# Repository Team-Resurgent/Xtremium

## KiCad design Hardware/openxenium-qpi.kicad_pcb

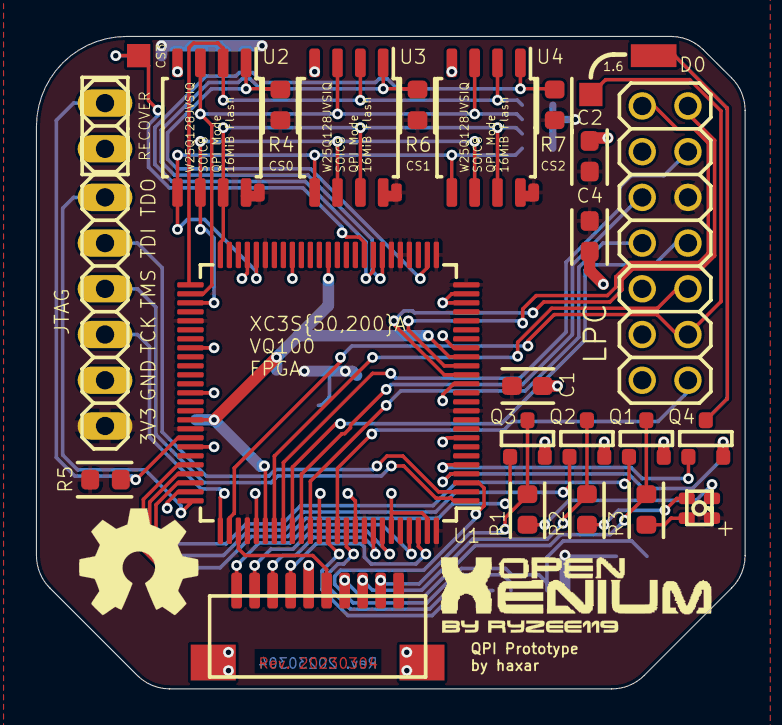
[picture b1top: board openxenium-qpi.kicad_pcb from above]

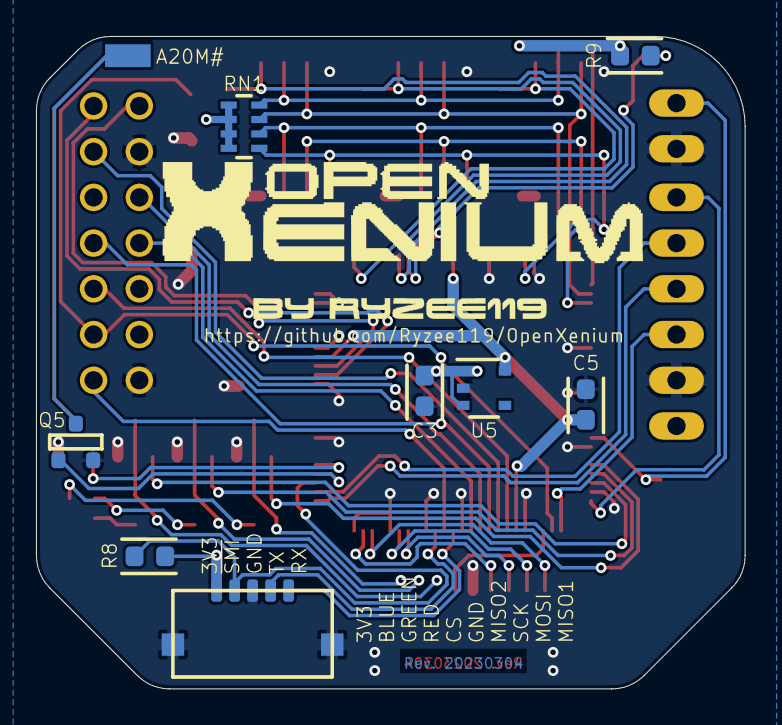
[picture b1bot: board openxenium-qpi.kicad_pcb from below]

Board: 2 copper layers, 39.4 x 36.2 mm, 39 parts (9 on the bottom side), 47 nets.

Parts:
A20M#: SMD1,27-2,54
C1, C2: 0.1uF; C0603
C3, C5: 1uF; C0603
C4: 10uF; C0603
D0: SMD1,27-2,54
J1: TE Connectivity 1-2367196-0; SM10B-SRSS-TB
J2: Molex 503763-0591; SM10B-SRSS-TB
JTAG: 1X06
L1: 19-237/R6GHBHC-A07/2T; 4-SMD-R6GHBHC
LPC: 2X07
OSHW Logo: OSHW-Symbol_6.7x6mm_SilkScreen
Q1, Q2, Q3, Q4, Q5: SOT-23
R1, R2, R3: 470; R0603
R4, R5, R6, R7, R8, R9: 10k; R0603
RECOVERY: 1X02
RN1: 10k; R_Array_Concave_4x0603
TP1, TP2: TPTP13SQ; TP13SQ
U1: VQFP-100_14x14mm_P0.5mm
U2, U3, U4: SOIC-8_5.23x5.23mm_P1.27mm
U5: onsemi NCV8164ASN120T1G; TSOP-5_1.65x3.05mm_P0.95mm
VCC1, VCC2, VCC3: SMD-Pad_0.6x1mm

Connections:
+1V2: C5.2, U1.17, U1.38, U1.66, U1.81, U5.5
+3V3: C1.1, C2.1, C3.1, C4.1, J1.10, J2.1, JTAG.1, L1.VCC, LPC.9, R4.1, R5.1, R6.1, R7.1, R8.2, R9.1, RN1.1, RN1.2, RN1.3, RN1.4, U1.11, U1.22, U1.25, U1.26, U1.29, U1.30, U1.31, U1.45, U1.55, U1.67, U1.79, U1.92, U1.96, U1.100, U2.8, U3.8, U4.8, U5.1, U5.3, VCC1.1, VCC2.1, VCC3.1
FTDI_RXD: J2.4, U1.90
FTDI_TXD: J2.5, U1.88
GND: C1.2, C2.2, C3.2, C4.2, C5.1, J1.5, J1.C1, J1.C2, J2.3, J2.C1, J2.C2, JTAG.2, LPC.2, LPC.12, Q1.2, Q2.2, Q3.2, Q4.2, Q5.2, RECOVERY.1, U1.8, U1.14, U1.18, U1.23, U1.24, U1.42, U1.47, U1.58, U1.63, U1.69, U1.74, U1.80, U1.87, U1.91, U1.95, U1.99, U2.4, U3.4, U4.4, U5.2
HEADER_CS: J1.6, U1.78
HEADER_LED_B: J1.9, Q3.1, R1.2
HEADER_LED_G: J1.8, Q2.1, R2.2
HEADER_LED_R: J1.7, Q1.1, R3.2
HEADER_MISO1: J1.1, U1.97
HEADER_MISO2: J1.4, U1.98
HEADER_MOSI: J1.2, U1.94
HEADER_SCK: J1.3, U1.93
LED_B: L1.B, R1.1
LED_G: L1.G, R2.1
LED_R: L1.R, R3.1
LPC_CLK: LPC.1, U1.89
LPC_LAD0: LPC.11, U1.83
LPC_LAD1: LPC.10, U1.85
LPC_LAD2: LPC.8, U1.86
LPC_LAD3: LPC.7, U1.84
LPC_LFRAME: LPC.3, TP1.TP, U1.77
LPC_RST: LPC.5, U1.82
MOSFET_A20M: Q5.3, U1.4
MOSFET_D0: Q4.3, U1.5
MOSFET_LED_B: Q3.3, U1.71
MOSFET_LED_G: Q2.3, U1.72
MOSFET_LED_R: Q1.3, U1.73
PAD_A20M: A20M#.1, Q5.1
PAD_D0: D0.1, Q4.1
QPI_CLK: U1.53, U2.6, U3.6, U4.6
QPI_CS0: R4.2, U1.27, U2.1
QPI_CS1: R6.2, U1.32, U3.1
QPI_CS2: R7.2, U1.33, U4.1
QPI_CS3: R9.2, TP2.TP, U1.34
QPI_IO0: RN1.5, U1.46, U2.5, U3.5, U4.5
QPI_IO1: RN1.8, U1.51, U2.2, U3.2, U4.2
QPI_IO2: RN1.7, U1.52, U2.3, U3.3, U4.3
QPI_IO3: RN1.6, U1.50, U2.7, U3.7, U4.7
SCL: LPC.13, U1.15
SDA: LPC.14, U1.16
SWITCH_RECOVER: R5.2, RECOVERY.2, U1.68
TCK: JTAG.3, U1.76
TDI: JTAG.5, U1.2
TDO: JTAG.6, U1.75
TMS: JTAG.4, U1.1
~SMI: J2.2, R8.1, U1.3

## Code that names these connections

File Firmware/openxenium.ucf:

# Created by Constraints Editor (xc9572xl-vq64-10) - 2019/09/20
# Updated for QPI support (xc3s{50,200}a-vq100) - 2022/04/04

# Applies to Spartan-3A and Spartan-6 devices.
CONFIG VCCAUX=3.3;
# Prohibit the automatic placement of dual purpose pins that are connected to VCC or GND for configuration.
CONFIG PROHIBIT=P99; # HSWAP/PUDC_B
CONFIG PROHIBIT=P25; # M0
CONFIG PROHIBIT=P23; # M1
CONFIG PROHIBIT=P24; # M2
CONFIG PROHIBIT=P31; # VS0
CONFIG PROHIBIT=P30; # VS1
CONFIG PROHIBIT=P29; # VS2

NET "LPC_CLK" TNM_NET = LPC_CLK;
TIMESPEC TS_LPC_CLK = PERIOD "LPC_CLK" 33 Mhz HIGH 50%;

NET "QPI_CLK" LOC="P53" | IOSTANDARD=LVCMOS33; # CCLK
NET "QPI_IO<0>" LOC="P46" | IOSTANDARD=LVCMOS33; # MOSI
NET "QPI_IO<1>" LOC="P51" | IOSTANDARD=LVCMOS33; # DIN
NET "QPI_IO<2>" LOC="P52" | IOSTANDARD=LVCMOS33;
NET "QPI_IO<3>" LOC="P50" | IOSTANDARD=LVCMOS33;
NET "QPI_CS<0>" LOC="P27" | IOSTANDARD=LVCMOS33; # CSO_B @ U2/CS0
NET "QPI_CS<1>" LOC="P32" | IOSTANDARD=LVCMOS33; # @ U3/CS1
NET "QPI_CS<2>" LOC="P33" | IOSTANDARD=LVCMOS33; # @ U4/CS2
NET "QPI_CS<3>" LOC="P34" | IOSTANDARD=LVCMOS33; # @ CS3
NET "LPC_CLK" LOC="P89" | IOSTANDARD=LVCMOS33 | BUFG=CLK;
NET "LPC_RST" LOC="P82" | IOSTANDARD=LVCMOS33;
NET "LPC_LFRAME" LOC="P77" | IOSTANDARD=LVCMOS33;
NET "LPC_LAD<0>" LOC="P83" | IOSTANDARD=LVCMOS33;
NET "LPC_LAD<1>" LOC="P85" | IOSTANDARD=LVCMOS33;
NET "LPC_LAD<2>" LOC="P86" | IOSTANDARD=LVCMOS33;
NET "LPC_LAD<3>" LOC="P84" | IOSTANDARD=LVCMOS33;
NET "HEADER_MISO1" LOC="P97" | IOSTANDARD=LVCMOS33;
NET "HEADER_MISO2" LOC="P98" | IOSTANDARD=LVCMOS33;
NET "HEADER_CS" LOC="P78" | IOSTANDARD=LVCMOS33;
NET "HEADER_SCK" LOC="P93" | IOSTANDARD=LVCMOS33;
NET "HEADER_MOSI" LOC="P94" | IOSTANDARD=LVCMOS33;
NET "MOSFET_LED_R" LOC="P73" | IOSTANDARD=LVCMOS33; # @ Q1
NET "MOSFET_LED_G" LOC="P72" | IOSTANDARD=LVCMOS33; # @ Q2
NET "MOSFET_LED_B" LOC="P71" | IOSTANDARD=LVCMOS33; # @ Q3
NET "MOSFET_D0" LOC="P5" | IOSTANDARD=LVCMOS33; # @ Q4
NET "MOSFET_A20M" LOC="P4" | IOSTANDARD=LVCMOS33; # @ Q5
NET "SWITCH_RECOVER" LOC="P68" | IOSTANDARD=LVCMOS33;
#NET "JTAG_TMS" LOC="P1" | IOSTANDARD=LVTTL | DRIVE=8 | SLEW=FAST;
#NET "JTAG_TCK" LOC="P76" | IOSTANDARD=LVTTL | DRIVE=8 | SLEW=FAST;
#NET "JTAG_TDI" LOC="P2" | IOSTANDARD=LVTTL | DRIVE=8 | SLEW=FAST;
#NET "JTAG_TDO" LOC="P75" | IOSTANDARD=LVTTL | DRIVE=8 | SLEW=FAST;
NET "FTDI_TXD" LOC="P88" | IOSTANDARD=LVTTL; # RX
NET "FTDI_RXD" LOC="P90" | IOSTANDARD=LVTTL | DRIVE=4 | SLEW=SLOW; # TX
#NET "SMI" LOC="P3" | IOSTANDARD=LVCMOS33;
#NET "SCL" LOC="P15" | IOSTANDARD=LVCMOS33;
#NET "SDA" LOC="P16" | IOSTANDARD=LVCMOS33;

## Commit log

2021-05-14 FW: Ignore unsupported LPC IO addresses (disables TSOPBOOT to fit)
2022-04-14 FW: Preliminary QPI support (with LPC peripheral support)
2022-04-14 FW: Overlay LPC bus activity on the LED
2022-04-14 FW: Reduce syncing stage wait states for IO transactions
2022-04-20 FW: Add A20M# support
2022-04-27 FW: Implement bank & chip selection
2022-04-27 FW: nit: Decrease indent for case statements (same for C style switch)
2022-04-29 FW: Add SDP support (disables bank selection for lack of pterms)
2022-04-30 FW: Compress bank select logic (now it fits)
2022-04-30 FW: Use a custom type for QPI enable
2022-05-01 FW: Move banks to bottom of flash
2022-05-04 FW: Check busy bit when switching chips
2022-05-07 After building, testing & realizing the chips don't power-up in QPI mode & design needs a Spartan-3E instead
2022-05-11 FW: Use Spartan-3A VQ100 package
2022-05-12 FW: Initialize QPI mode for all chips at power-up
2022-05-12 FW: Relocate user banks to reserve 1MiB at bottom of flash for FPGA bitstream
2022-05-12 FW: Set VCCAUX constraint
2022-05-13 HW: Update BOM
2022-05-21 FW: Show which chip is selected via banking register
2022-05-30 FW: Add bitbang IO mode for QPI bus
2022-05-30 FW: Finally fix Read Status Register-1 & Page Program (delay logic did nothing)
2022-06-01 FW: Ensure QPI mode is set at power-up
2022-06-07 FW: Prevent edge case of overwriting IO registers when determining LPC cycle type
2022-06-07 FW: Harden QPI bitbang IO register access
2022-06-07 FW: Add end sector erase logic for RECOVER bank
2022-06-09 FW: SDP command sequence addressing is actually 12 bits wide
2022-06-25 FW: Prevent race condition by adding stop state for end sector erase logic
2022-06-25 FW: Add CFI ROM logic (now boots to XOS)
2022-07-05 HW: Import Rev. 20220704 QPI board
2022-07-24 HW: Include wire housings & contacts in BOM
2022-07-24 HW: Include right-angle header for D0 & A20M# in BOM
2022-07-27 HW: nit: Consolidate edge cut line breaks
2023-03-06 FW: Refactor & assign `CS3` QPI auxiliary chip select signal
2023-03-06 FW: Rearrange FPGA pins 3,4,5 (breaks compat with Rev. 20220704 QPI board)
2023-03-06 HW: Import Rev. 20230304 QPI board
2023-03-07 FW: Add a 96MHz DCM
2023-03-08 FW: Simplify TSC logic
2023-03-08 FW: Preliminary UART TX support (to FTDI at 3Mbps via 96MHz DCM)
2023-03-09 FW: Fix LPC bus master arbitration when detecting SuperIO
2023-03-09 FW: Improve LFRAME detection
2023-03-09 FW: nit: Renaming
2023-03-10 FW: nit: Refactor LPC address
2023-03-11 FW: Add UART Scratch Register
2023-03-11 FW: Show UART TX activity on green LED
2023-03-13 FW: nit: Shorten signal names
2023-03-13 FW: Implement SDP Unlock Bypass write mode
2023-03-13 FW: Correct DCM output clock period from 96.96MHz to 96MHz
2023-03-25 FW: Prevent bank/chip selection when in a SDP state
2023-05-10 FW: Fix UART TX corruption edge case
2023-05-10 FW: Fix UART TX duplication edge case
2023-05-11 FW: Fix another UART TX duplication edge case
2023-05-12 FW: Fix UART TX to one stop bit (saturation speedup by 33KiB/s; was right the first time)
2024-05-30 Added: port to identify xtremium variant

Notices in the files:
Hardware/openxenium-qpi.kicad_pcb:
Licensed under CERN OHL v.1.2 or later
